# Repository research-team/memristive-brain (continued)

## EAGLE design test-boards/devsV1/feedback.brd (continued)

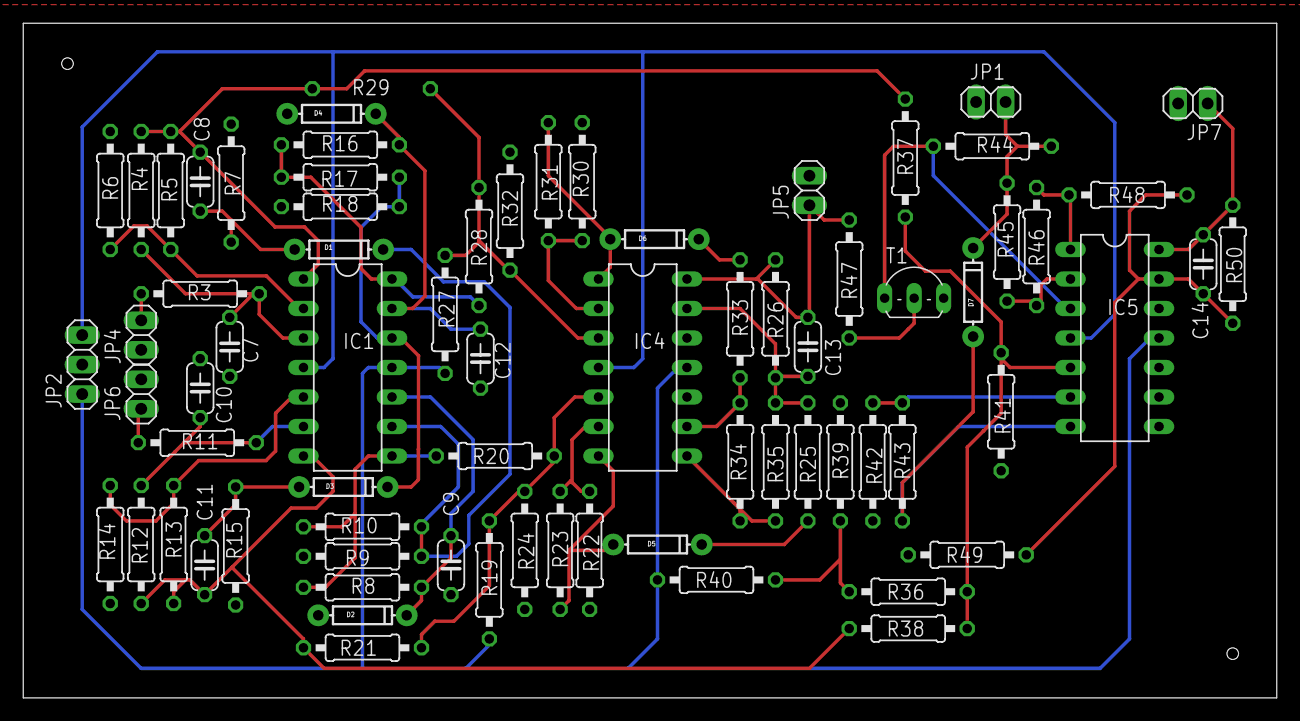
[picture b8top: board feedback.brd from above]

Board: 2 copper layers, 107.9 x 58.1 mm, 73 parts (1 on the bottom side), 42 nets.

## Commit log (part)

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2019-04-08 SCS: complete Gantt for article
2019-04-08 more experiments
    added jupyter checkpoints to gitignore
    removed checkpoints
    added resistance measurement
    N: complete Gantt for N article
    N: updated plan
    SCS: complete Gantt for article
2019-04-08 MN: started Gantt
2019-04-08 MN: completed Gantt
2019-04-09 restored pwm with invertor
2019-04-09 removed unsued generator
2019-04-09 team: fixed actual bug
2019-04-10 Added scripts for memristor experiment
2019-04-10 fixed fall concatenation and added equipment command sheets
2019-04-11 added draft for new pwm schematic
2019-04-12 added new experiments
2019-04-12 little script reworking
2019-04-15 -0,2-0,15V Testbench
2019-04-15 Gantts update
2019-04-15 removed excess output
2019-04-16 little ordering
2019-04-16 making projects more comfortable to use
2019-04-16 added .idea folder to .gitignore
2019-04-16 balanced bipolar pwm
2019-04-17 CPG, N: updated plan
2019-04-18 removed some of excessive power levels
2019-04-18 MN: added refractory negative feedback
2019-04-18 MN: updated several diagrams
2019-04-18 MN: added neromodulator
2019-04-22 Removed unsued templates
2019-04-24 added twin-diode configuration
2019-04-25 MN: started motifs
2019-04-29 added special classes for oscilloscope and generator
2019-04-30 added setup for pwm test
2019-05-06 added test results for complete schematic
2019-05-07 added new full test memristor measurement
2019-05-08 added half of experiment results
2019-05-08 added low half of results
2019-05-09 chaged plot names
2019-05-09 changed resistance phase name to proper one
2019-05-09 output cleared
2019-05-09 add mem3 fresh hyst plot
2019-05-09 cleared output cell
2019-05-14 leakage reworked, added some tests to it
2019-05-15 added resistors to leakage and some useful scripts
2019-05-15 added some project files
2019-05-17 added custom class for rows
2019-05-17 changed some values to standart resistor lines
2019-05-31 added new hyst expreiment
2019-05-31 added some modificaions to custom trigger ordering script
2019-06-04 added some latest mem3 tests
2019-06-05 added preliminary results
2019-06-05 added few experiments
2019-06-05 reworked some pictures
2019-06-06 added 06.06.19 tests
2019-06-06 test
2019-06-07 added amplifier for 0.2 pre input
2019-06-13 add soma integrator for prorotype
2019-06-14 14.06.19 new data
2019-06-14 added ipynb to gitignore
2019-06-14 added some results
2019-06-15 added pic
2019-06-15 updated pic
2019-06-18 started teamlead guide
2019-06-18 Teamlead guide: completed who is teamlead section
2019-06-18 Teamlead guide: started documentation section
2019-06-18 Teamlead guide: started tasks management section
2019-06-18 Teamlead guide: started weekly activity
2019-06-18 Teamlead guide: completed weekly activity
2019-06-18 Teamlead guide: completed initial activity
2019-06-18 Teamlead guide: corrected link
2019-06-18 Teamlead guide: corrected links
2019-06-19 Update teamlead-guide.md
    added book
2019-06-20 Update teamlead-guide.md
    added new book
2019-06-20 added delays
2019-06-20 rearranged plans and team dirs -> doc
2019-06-20 nociception article plan updated
2019-06-20 CPG article plan update started
2019-06-20 added first version of latest combine schematic
2019-06-24 CPG article plan update completed
2019-06-25 added multiplyer to manage different signals
2019-06-26 add generator on timer NE555
2019-06-26 added MN
2019-06-26 one language name
2019-06-27 reduced pwm width and extended refactory period
2019-06-27 minor fixes
2019-06-27 final scheme
2019-06-27 changed some nominals
2019-06-28 added gantt
2019-06-28 2 final version
2019-07-01 ADD base config and SWEEP measurments
2019-07-01 UPDATE syntax for queries
2019-07-01 ADD script for long step test, by Amirkhan
2019-07-01 SET default buffer to first one and CALCULATE amount of points for two and one hour tests
2019-07-02 Colibrate scripts
2019-07-02 ADD data of 10 memristor 1 hour test
2019-07-02 2.07 results moved
2019-07-02 structure reworking
2019-07-02 Revert "structure reworking"
    This reverts commit ceaf0d5049a81069bff63f77c6d47813e8c67f15.
2019-07-02 structure rework fixed
2019-07-02 added first results on new memristor
2019-07-02 added results for memristor 10
2019-07-03 UPDATE settings
2019-07-03 RAW data of one hour test 2019-07-03
2019-07-03 ADD plots of 2 memristor, 1 hour test
2019-07-04 2 ух часовой прямолинейный эксперемент
2019-07-04 Temp changes inside anaconda
2019-07-04 new pictures
2019-07-05 ADD 1 memristor's 2 hour test linear
2019-07-05 ADD 1 memristor's plots 2 hour linear test
2019-07-05 Результаты эксперементов
2019-07-05 ADD plots of step 1 memristor
2019-07-08 multivibrator for counter
2019-07-09 Результаты 3 его мемристора
2019-07-10 Лесенка 4 мемристор
2019-07-11 4 и часть 12 мемристоры
2019-07-18 ээээээксперементы
2019-07-19 эксперементы
2019-07-19 added some pictures
2019-07-23 Plots of leakage in real world model
2019-07-25 results
2019-07-27 Leakage of full schema with configuration in names
2019-07-30 SCRIPTS for capture data from oscilographs, name - osci name
2019-07-30 изменения
2019-07-31 add payoff on scheme
2019-08-01 kick labels
2019-08-01 CHANGE refractor period to 5ms
2019-08-01 ADD sombrero real life pictures
2019-08-01 12 мемристор
2019-08-02 UPDATE and ADD plots of real life neuron
2019-08-02 UPDATE stable circuit
2019-08-02 fixed some sine error
2019-08-02 12, 10
2019-08-05 updated nonmem
2019-08-06 ADD plots of 4 memristor re-test
2019-08-06 updated adder
2019-08-08 ADD osci script fro retriving data
2019-08-09 13 memr plot
2019-08-12 more plots
2019-08-14 TEST memristors data
2019-08-14 04 plot
2019-08-15 photo
2019-08-16 photoes
2019-08-19 Dependency between learning speed and input layering
2019-08-20 ADD data of single, multi and zero spikes and RENAME phase test data
2019-08-21 05 plot
2019-08-26 ADD data for victor presentation
2019-08-27 updated resistors
2019-08-28 mem4_plot
2019-08-29 resistor
2019-09-05 step_13
2019-09-07 data
2019-09-08 code
2019-09-08 Added Untitled Diagram.drawio
2019-09-09 plot
2019-09-10 add flexor's scheme
2019-09-10 add flexor
2019-09-10 updated weights
2019-09-11 ADD scripts for osci and data plotting
2019-09-11 TEMP files for debugg script ( resistance in sceme = 3.8Mom)
2019-09-12 'ph'
2019-09-13 ADD data of memristor's learning by phase
2019-09-17 ADD new data and 3d plots scripts
2019-09-18 UPDATE graph_plot for dR/dT
2019-09-23 new scheme
2019-09-23 add OM5
2019-09-26 new voltage of outputs for ds5 stimulator
2019-10-08 new_memes
2019-10-09 correct the mistake
2019-10-11 new data
2019-10-11 new plot
2019-10-15 added memrs 4 and 5
2019-10-23 data7
2019-10-23 plot7
2019-10-23 Second meassurment of 7 memristor
2019-11-02 ADD plots for 3 memr after neuron learning
2019-11-05 DATA of 3 memristor neuron learning
2019-11-07 ADD new learning data 3 memristor
2019-11-13 PLOT data 2 memr 40%
2019-11-13 ADD pdf plots 2 and 4 memristor
2019-11-13 ADD 2 memr 10% plot data
2019-11-14 resistance data of 2 memr
2019-11-14 plot of 2 memr res
2019-11-14 second plot of memr2 res
2019-11-18 data of 4 memr after cycle test
2019-11-18 data of 2 memr after cycle test
2019-11-18 2 and 9 memr data after cycle test
2019-11-18 new 9 memr data of test
2019-11-19 memr 3, 5 cycle tests data
2019-11-19 6 memr cycle test data
2019-11-19 plots
2019-11-25 png of last memr test
2019-11-25 plots of memr
2019-11-25 photo of memr
2020-01-28 OLD plots
2020-01-28 NEW 3 memristors data
2020-01-28 0 memr data and plots
2020-01-28 2 memr data and plots
2020-01-28 3 memr data and plots
2020-01-28 5 memr data and plots
2020-01-28 Change plots title to dynamic
2020-01-28 ADD 6 memr data and plots
2020-01-28 ADD data and plots 7 memr
2020-01-28 ADD 4 memr data and plots
2020-04-02 created endstop
2020-04-02 repo cleaning
2020-09-23 added scripts
